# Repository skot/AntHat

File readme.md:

## AntHat

The AntHat is a HAT for a RaspberryPi to control Antminer fans and PSU. Best used with the aditBoard to fully control the miner.

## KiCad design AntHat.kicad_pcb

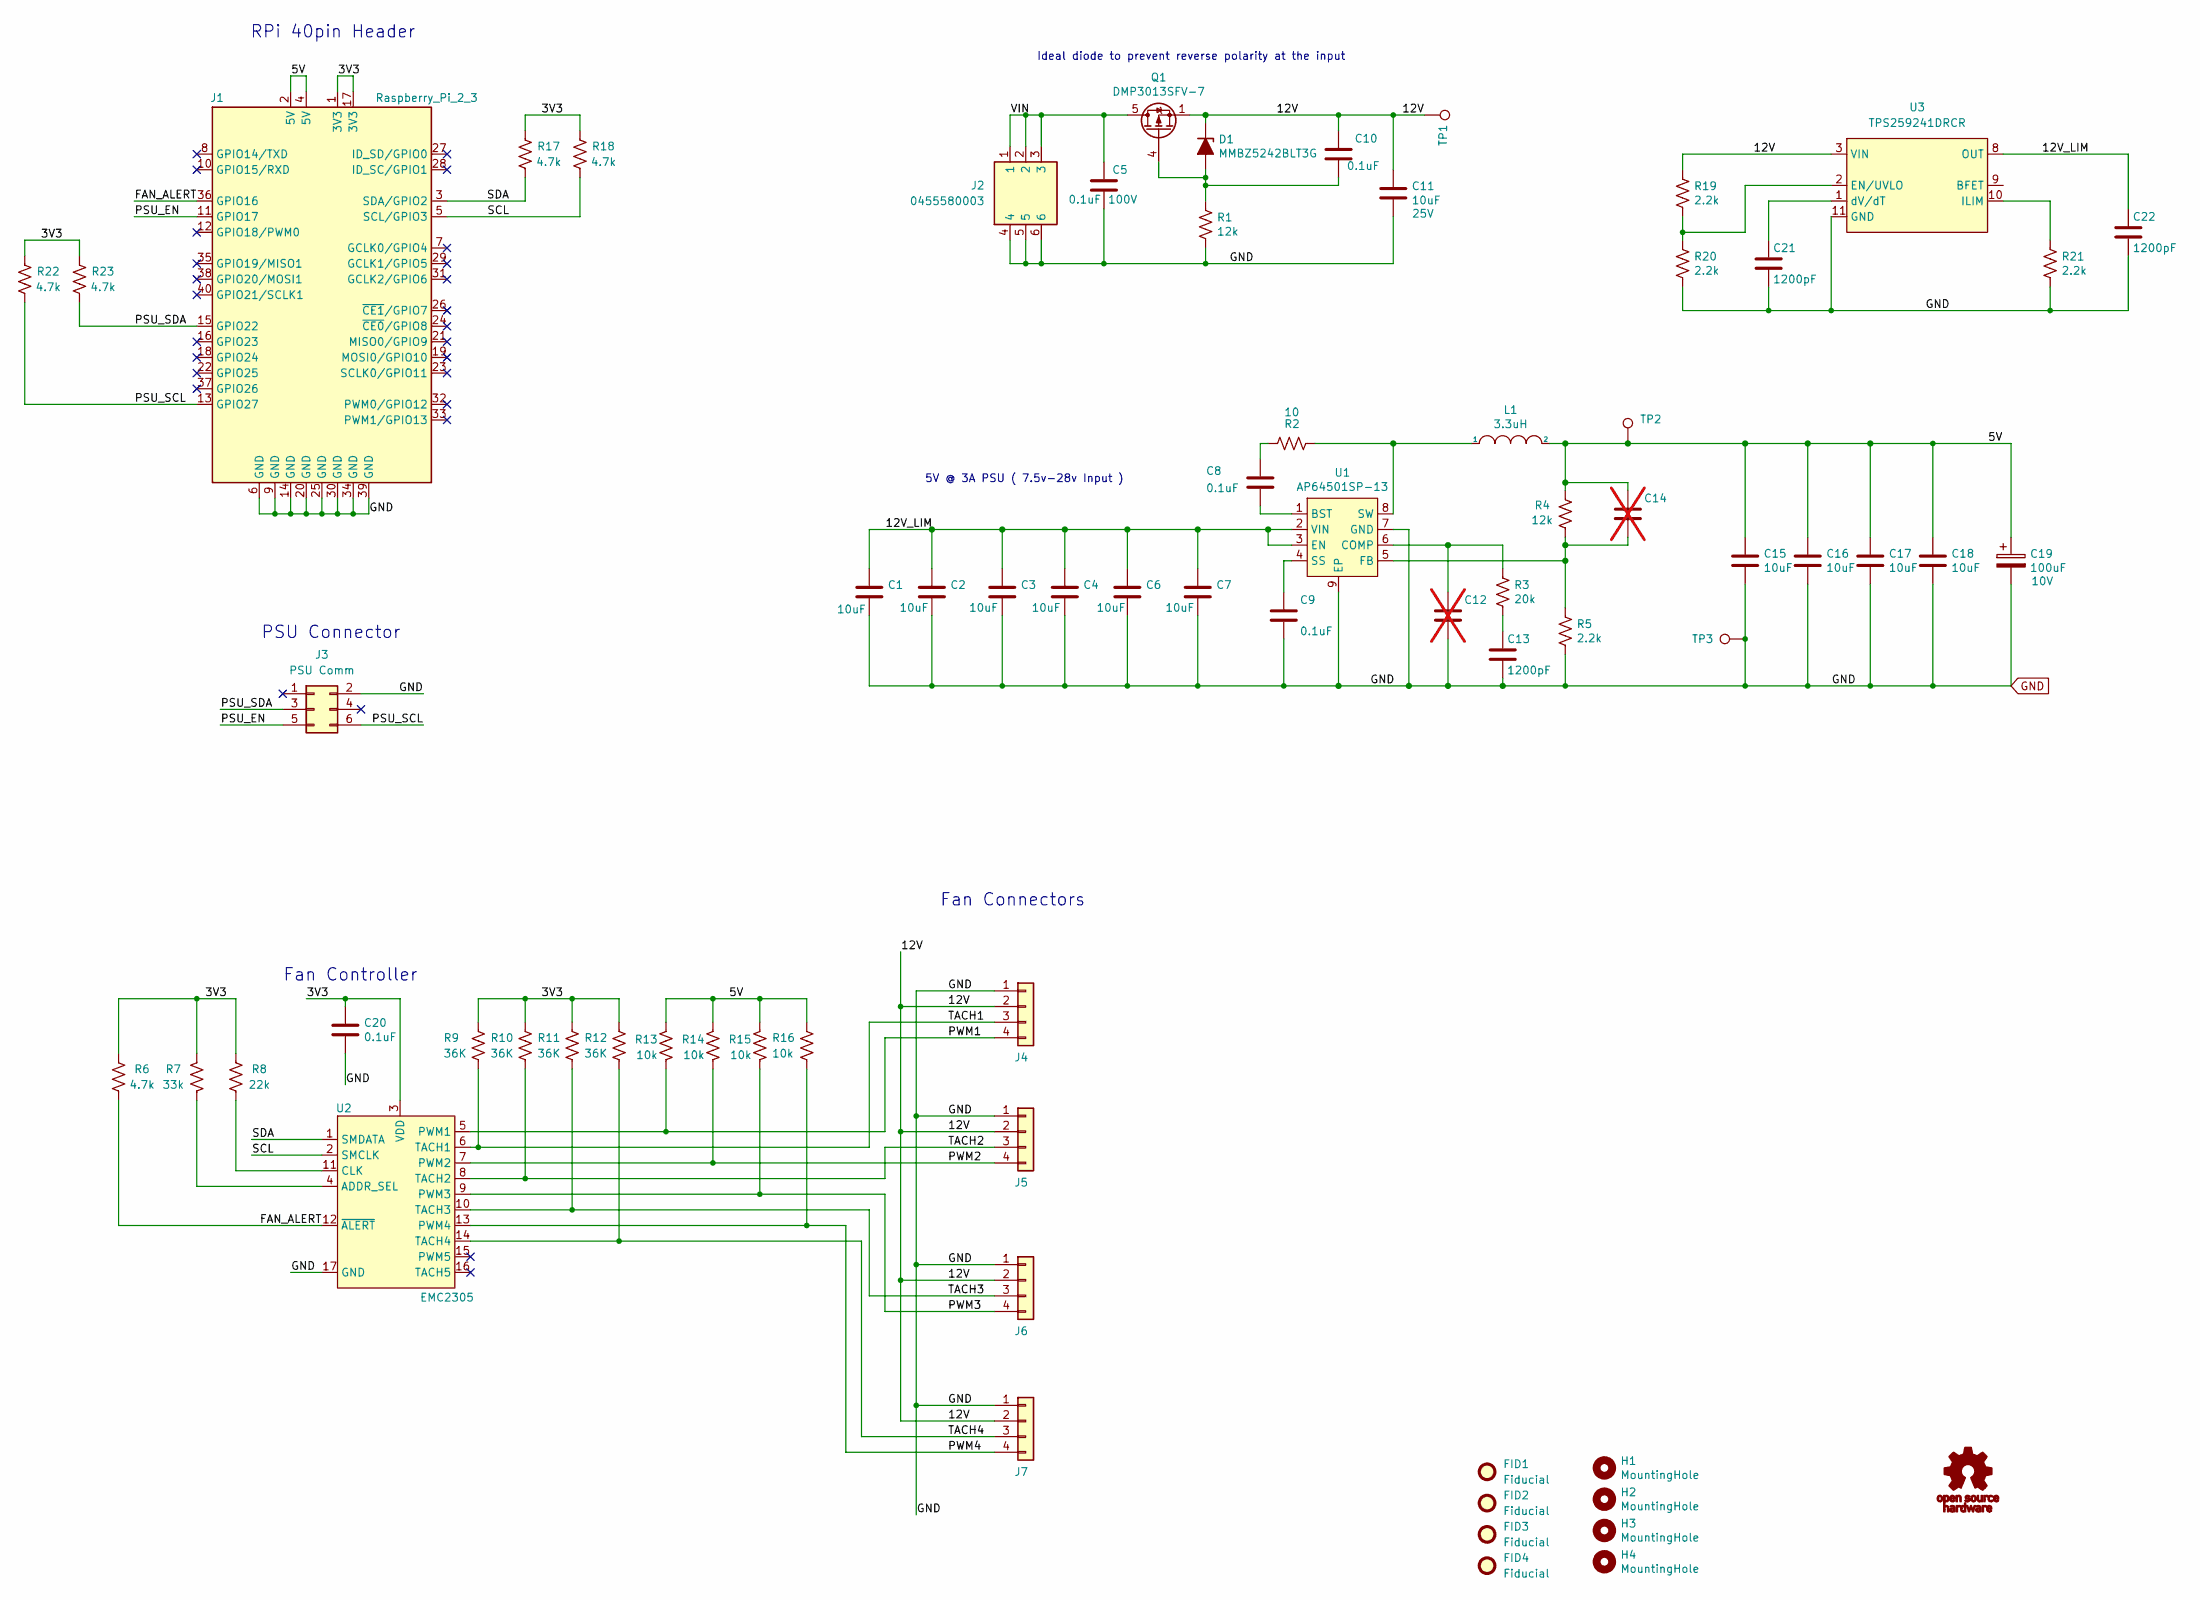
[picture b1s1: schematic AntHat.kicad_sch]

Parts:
C1, C2, C3, C4, C6, C7, C11, C15, C16, C17, C18: 10uF; C_0805_2012Metric; Voltage 25V; PARTNO GRM21BC8YA106ME11L; LCSC C15850
C5: 0.1uF; C_0805_2012Metric; Voltage 100V; LCSC C28233
C8, C9, C10, C20: 0.1uF; C_0402_1005Metric; Voltage 25V; PARTNO GRM155R71C104KA88J; LCSC C52923
C12, C14: C_0402_1005Metric; not fitted
C13, C22: 1200pF; C_0402_1005Metric; Voltage 25V; PARTNO GCM155R71H122KA37D; LCSC C16529
C19: 100uF; CP_EIA-7343-31_Kemet-D; Voltage 10V; PARTNO TAJD107K010RNJ; LCSC C7222
C21: 1200pF; C_0402_1005Metric; Voltage 25V; PARTNO GCM155R71H122KA37D; LCSC C107021
D1: MMBZ5242BLT3G; D_SOT-23_ANK; PARTNO LBZX84C12LT1G; LCSC C12773
FID1, FID2, FID3, FID4: Fiducial; Fiducial_0.5mm_Mask1mm
G2: OSHWA-LOGO; oshwa_logo
H1, H2, H3, H4: MountingHole; MountingHole_2.7mm_M2.5
J1: Raspberry_Pi_2_3; ESQ-120-14-T-D; PARTNO PPPC202LFBN-RC; LCSC C2977589
J2: 0455580003; PARTNO 0455580003; LCSC C492365
J3: PSU Comm; CONN-TH_6P-P2.00_PHD-2X3A; PARTNO SWR204-NRTN-D03-ST-GA; LCSC C2845614
J4, J5: 61900411021; MOLEX_1x4_2x2_combo; PARTNO 61900411021; LCSC C2982043
J6, J7: 0353180420; MOLEX_1x4_2x2_combo; PARTNO 0353180420; LCSC C54909
L1: 3.3uH; IND-SMD_L5.7-W5.2; PARTNO SRP5030T-3R3M; LCSC C189931
Q1: DMP3013SFV-7; Diodes_PowerDI3333-8; PARTNO DMP3013SFV-7; LCSC C264098
R1, R4: 12k; R_0402_1005Metric; PARTNO RC0402FR-0712KL; LCSC C25752
R2: 10; R_0402_1005Metric; PARTNO RC0402FR-0710RL; LCSC C25077
R3: 20k; R_0402_1005Metric; PARTNO RC0402FR-0720KL; LCSC C25765
R5, R19, R20, R21: 2.2k; R_0402_1005Metric; PARTNO RC0402FR-072K2L; LCSC C25879
R6, R17, R18, R22, R23: 4.7k; R_0402_1005Metric; PARTNO RC0402FR-074K7L; LCSC C25900
R7: 33k; R_0402_1005Metric; PARTNO RC0402FR-0733KL; LCSC C25779
R8: 22k; R_0402_1005Metric; PARTNO RC0402FR-0722KL; LCSC C25768
R9, R10, R11, R12: 36K; R_0402_1005Metric; PARTNO RC0402FR-0736KL; LCSC C137999
R13, R14, R15, R16: 10k; R_0402_1005Metric; PARTNO RC0402FR-0710KL; LCSC C60489
TP1, TP2, TP3: TestPoint; TestPoint_Pad_D1.5mm
U1: AP64501SP-13; SOIC-8-1EP_3.9x4.9mm_P1.27mm_EP2.95x4.9mm_Mask2.71x3.4mm_Th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; PARTNO AP64501SP-13; LCSC C2071517
U2: EMC2305; QFN16_4x4MC_MCH; PARTNO EMC2305-1-AP-TR; LCSC C621415
U3: TPS259241DRCR; VSON-10_L3.0-W3.0-P0.50-TL-EP; PARTNO TPS259241DRCR; LCSC C165131

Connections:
/3V3: C20.1, J1.1 (3V3), J1.17 (3V3), R6.2, R7.2, R8.2, R9.1, R10.1, R11.1, R12.1, R17.2, R18.2, R22.2, R23.2, U2.3 (VDD)
/5V: C14.1, C15.1, C16.1, C17.1, C18.1, C19.1, J1.2 (5V), J1.4 (5V), L1.2, R4.1, R13.1, R14.1, R15.1, R16.1, TP2.1
/12V: C10.1, C11.1, D1.3 (K), J4.2, J5.2, J6.2, J7.2, Q1.1 (S), Q1.2 (S), Q1.3 (S), R19.1, TP1.1, U3.3 (VIN), U3.4 (VIN), U3.5 (VIN)
/12V_LIM: C1.1, C2.1, C3.1, C4.1, C6.1, C7.1, C22.1, U1.2 (VIN), U1.3 (EN), U3.6 (OUT), U3.7 (OUT), U3.8 (OUT)
/FAN_ALERT: J1.36 (GPIO16), R6.1, U2.12 (~ALERT)
/PSU_EN: J1.11 (GPIO17), J3.5
/PSU_SCL: J1.13 (GPIO27), J3.6, R22.1
/PSU_SDA: J1.15 (GPIO22), J3.3, R23.1
/PWM1: J4.4, R13.2, U2.5 (PWM1)
/PWM2: J5.4, R14.2, U2.7 (PWM2)
/PWM3: J6.4, R15.2, U2.9 (PWM3)
/PWM4: J7.4, R16.2, U2.13 (PWM4)
/SCL: J1.5 (SCL/GPIO3), R18.1, U2.2 (SMCLK)
/SDA: J1.3 (SDA/GPIO2), R17.1, U2.1 (SMDATA)
/TACH1: J4.3, R9.2, U2.6 (TACH1)
/TACH2: J5.3, R10.2, U2.8 (TACH2)
/TACH3: J6.3, R11.2, U2.10 (TACH3)
/TACH4: J7.3, R12.2, U2.14 (TACH4)
/VIN: C5.1, J2.1, J2.2, J2.3, Q1.5 (D)
GND: C1.2, C2.2, C3.2, C4.2, C5.2, C6.2, C7.2, C9.2, C11.2, C12.2, C13.2, C15.2, C16.2, C17.2, C18.2, C19.2, C20.2, C21.2, C22.2, J1.6 (GND), J1.9 (GND), J1.14 (GND), J1.20 (GND), J1.25 (GND), J1.30 (GND), J1.34 (GND), J1.39 (GND), J2.4, J2.5, J2.6, J3.2, J4.1, J5.1, J6.1, J7.1, R1.2, R5.2, R20.2, R21.2, TP3.1, U1.7 (GND), U1.9 (EP), U2.17 (GND), U3.11 (GND)
unnamed: C8.1, R2.2
unnamed: C13.1, R3.2
unnamed: C10.2, D1.1 (A), Q1.4 (G), R1.1
unnamed: C8.2, U1.1 (BST)
unnamed: C12.1, R3.1, U1.6 (COMP)
unnamed: C14.2, R4.2, R5.1, U1.5 (FB)
unnamed: C9.1, U1.4 (SS)
unnamed: L1.1, R2.1, U1.8 (SW)
unnamed: R7.1, U2.4 (ADDR_SEL)
unnamed: R8.1, U2.11 (CLK)
unnamed: R19.2, R20.1, U3.2 (EN/UVLO)
unnamed: R21.1, U3.10 (ILIM)
unnamed: C21.1, U3.1 (dV/dT)

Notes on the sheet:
RPi 40pin Header
Ideal diode to prevent reverse polarity at the input
5V @ 3A PSU ( 7.5v-28v Input )
Fan Connectors
PSU Connector
Fan Controller

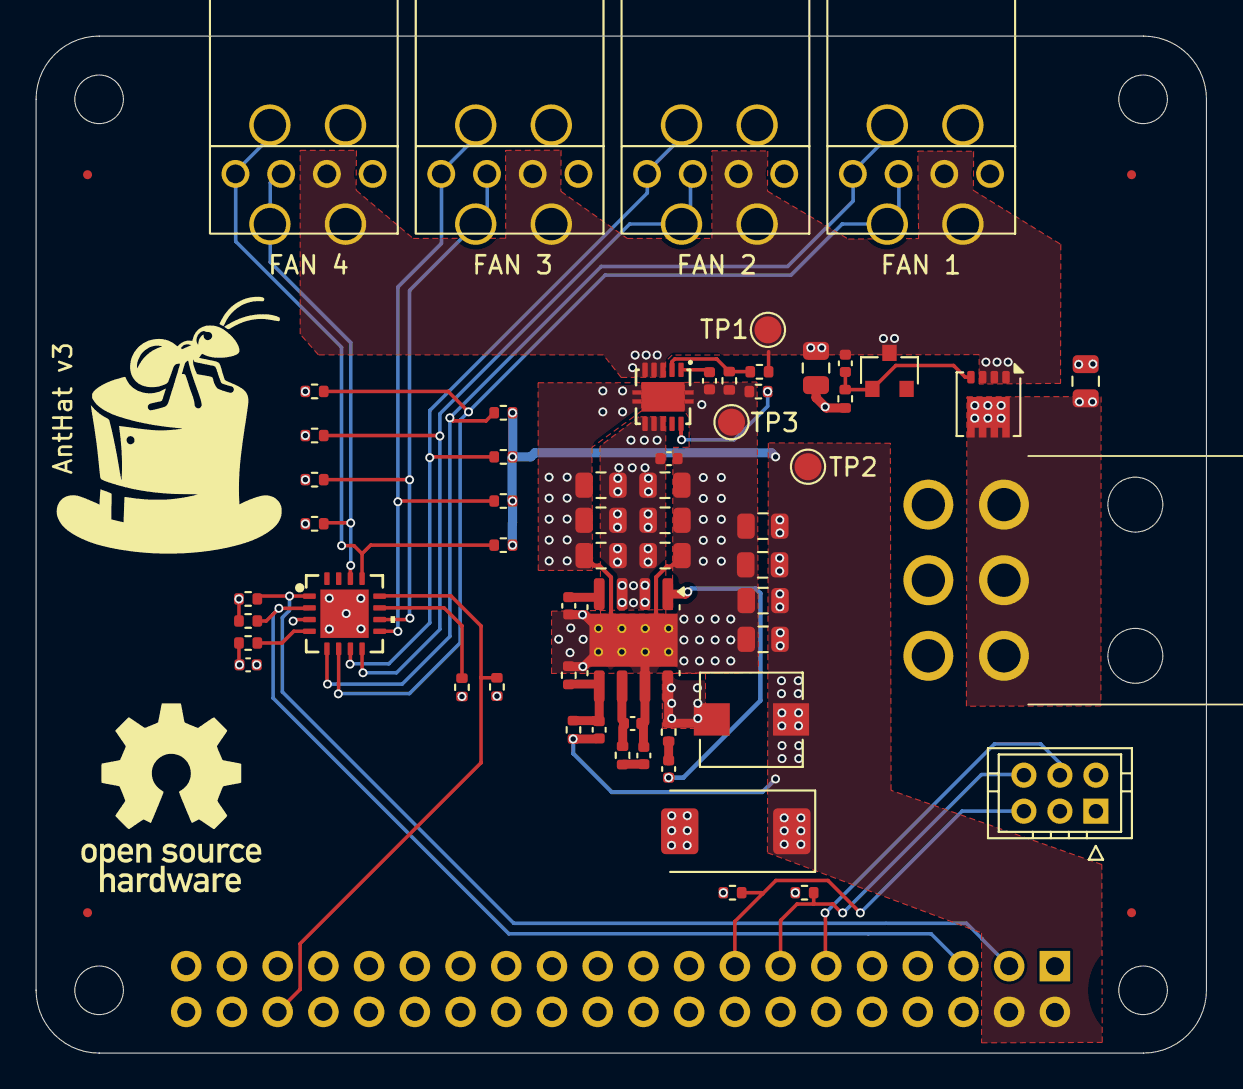
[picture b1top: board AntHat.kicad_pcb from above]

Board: 6 copper layers, 65.0 x 56.5 mm, 70 parts (0 on the bottom side), 33 nets.

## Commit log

2024-03-28 initial import
2024-03-28 finished routing. added logo
2024-03-28 add readme
2024-03-29 added the TPS54531 since the AP64501SP-13 isn't on DK. prolly will delete
2024-03-30 deleted TPS54531. Changed OOS Inductor. DRC passes
2024-04-04 DRC, ERC and added gerbers
2024-04-20 adding iBOM
2024-04-20 update iBOM
2024-04-20 add fix for #1
2024-05-06 started to add TPS259241
2025-01-22 combined the fan connector styles. added some LCSC part numbers. switched PSU I2C over to GPIO for bit banging.
2025-01-22 add inductor 3d model. update render
2025-01-22 better render
2025-01-22 fixed the footprint & paste on the TPS259241 footprint. Generated and checked gerbers. Generated BOM. Generated iBOM
2025-01-23 added JLCPCB Parts to BOM. changed one CAP to bigger size, cleaned up layout. regenerated gerbers, BOM and CPOS
2025-01-23 updated some OOS LCSC parts. regenerated BOM. added iBOM
2025-09-21 switched to 6 layers. moved power vias into pads
2025-09-21 added OSHWA logo. removed old gerbers
2025-09-22 added fiducials
2025-09-22 added 3d models. updated render
2025-09-22 add gerbers
2025-09-22 add BOM add iBOM
